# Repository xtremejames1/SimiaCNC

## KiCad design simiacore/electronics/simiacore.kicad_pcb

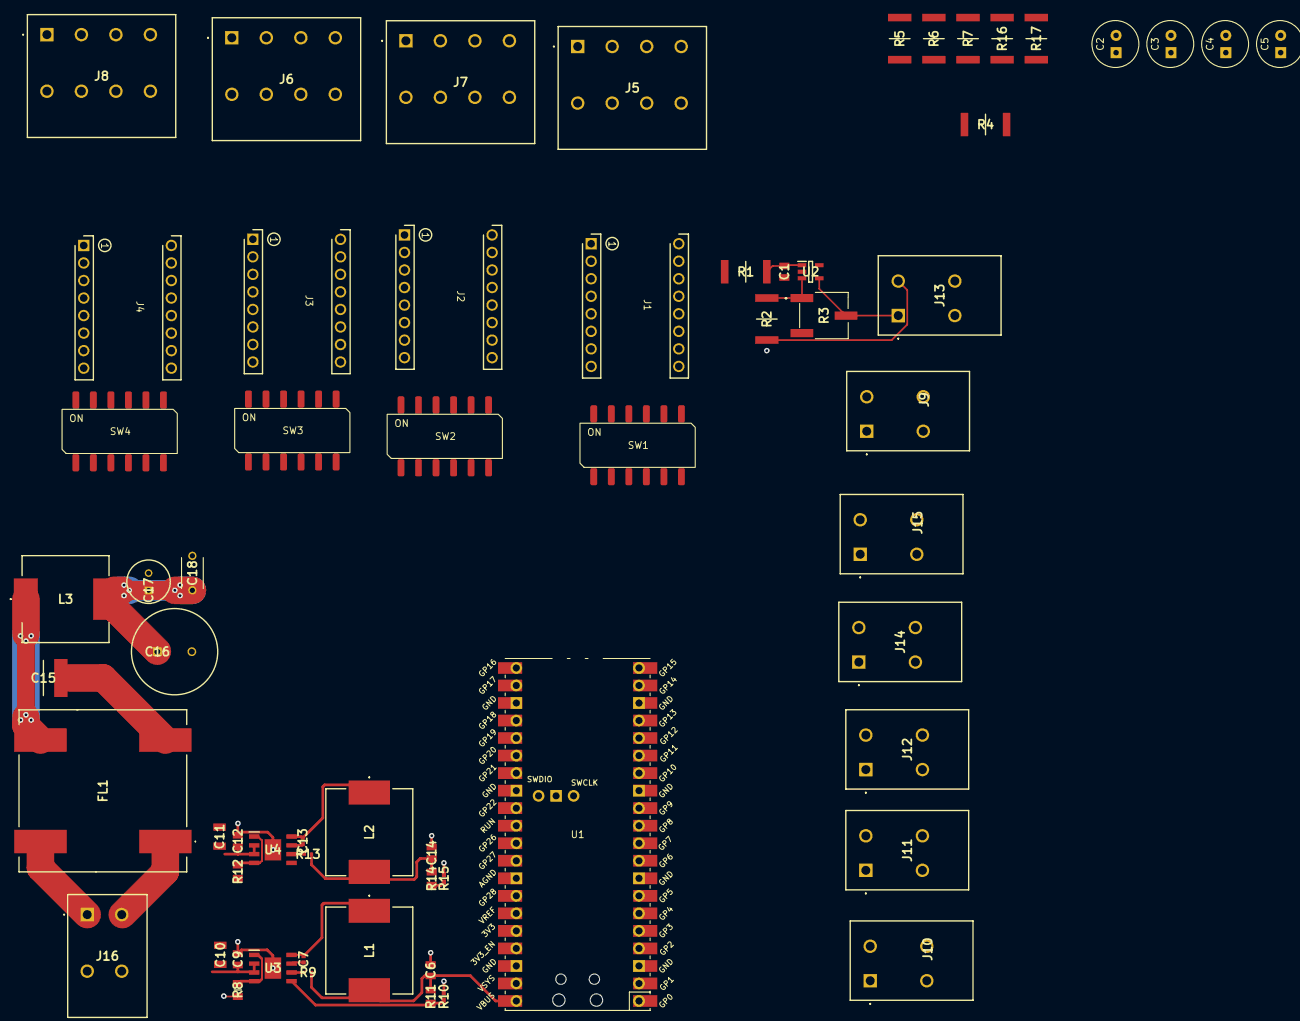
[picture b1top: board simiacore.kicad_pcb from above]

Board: 2 copper layers, 62 parts (0 on the bottom side), 75 nets.

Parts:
C1: 10uF; CAPC2012X145N
C2, C3, C4, C5: 100uF; MAL203859101E3
C6: 47uF; CAPC2012X145N
C7, C13: 100nF; CAPC1005X55N
C9, C12: 100nF; CAPC2012X145N
C10, C11: 3.3uF; CAPC3216X180N
C14: 22uF; CAPC2012X145N
C15: 22uF; CAPC6153X670N
C16: 330uF; CAPPRD500W65D1250H2700
C17: 10uF; CAPPRD250W50D630H1250
C18: 330nF; RDE5C1H103J1K1H03B
FL1: 240uH; PA5141305NLT
J1: X_STEP_DRIVER; 16pinStepperDriverHeader
J2: Y0_STEP_DRIVER; 16pinStepperDriverHeader
J3: Z_STEP_DRIVER; 16pinStepperDriverHeader
J4: Y1_STEP_DRIVER; 16pinStepperDriverHeader
J5: X_STEP; 1190299
J6: Y0_STEP; 1190299
J7: Z_STEP; 1190299
J8: Y1_STEP; 1190299
J9: X_LIM_PORT; 1190297
J10: Y0_LIM_PORT; 1190297
J11: Z_LIM_PORT; 1190297
J12: Y1_LIM_PORT; 1190297
J13: SPINDLE_SPEED; 1190297
J14: CYCLE_START_PORT; 1190297
J15: FEED_HOLD_PORT; 1190297
J16: 48VIN; 1190297
L1: 33uH; SRP1265WA4R7M
L2: 68uH; SRP1265WA4R7M
L3: 4.7uH; SRP1265WA4R7M
R1, R2: 1.5k; RESC6432X65N
R3: 5k_TRIM; 3361P1502GLF
R4, R5, R6, R7, R16, R17: 4.7k; RESC6432X65N
R8, R12: 64.9k; RESC2012X60N
R9, R13: 100k; ERJ2RKD1004X
R10, R15: 10k; RESC1005X35N
R11: 40.2k; RESC2012X60N
R14: 110k; RESC2012X60N
SW1, SW2, SW3, SW4: LOGIC_TOGGLE; CFS-0600TB
U1: PicoW; RPi_PicoW_SMD_TH
U2: NCS20231SN2T1G; SOT95P275X110-5N
U3, U4: LMR38010SDDAR; SOIC127P600X170-9N

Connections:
+3.3V: R4.1, R5.1, R6.1, R7.1, R16.1, R17.1, SW1.1, SW1.2, SW1.3, SW1.4, SW1.5, SW1.6, SW2.1, SW2.2, SW2.3, SW2.4, SW2.5, SW2.6, SW3.1, SW3.2, SW3.3, SW3.4, SW3.5, SW3.6, SW4.1, SW4.2, SW4.3, SW4.4, SW4.5, SW4.6, U1.36 (3V3)
+5V: C6.1, L1.2, R9.2, R11.1, U1.40 (VBUS)
+12V: C14.1, L2.2, R13.2, R14.1, U2.5 (VDD)
+48V: C2.1, C3.1, C4.1, C5.1, C9.1, C10.1, C11.1, C12.1, C16.1, C17.1, C18.1, J1.16, J2.16, J3.16, J4.16, L3.2, U3.2 (EN), U3.3 (VIN), U4.2 (EN), U4.3 (VIN)
/CYCLE_START: J14.1, R16.2, U1.22 (GPIO17)
/FEED_HOLD: J15.1, R17.2, U1.21 (GPIO16)
/Power Delivery/VIN: FL1.4, J16.1
/SPINDLE_PWM: R1.1, U1.20 (GPIO15)
/STEP_ENBL: J1.1, J2.1, J3.1, J4.1, U1.19 (GPIO14)
/Stepper Motor Drivers/X_A+: J1.11, J5.1
/Stepper Motor Drivers/X_A-: J1.12, J5.2
/Stepper Motor Drivers/X_B+: J1.14, J5.3
/Stepper Motor Drivers/X_B-: J1.13, J5.4
/Stepper Motor Drivers/Y0_A+: J2.11, J6.1
/Stepper Motor Drivers/Y0_A-: J2.12, J6.2
/Stepper Motor Drivers/Y0_B+: J2.14, J6.3
/Stepper Motor Drivers/Y0_B-: J2.13, J6.4
/Stepper Motor Drivers/Y1_A+: J4.11, J8.1
/Stepper Motor Drivers/Y1_A-: J4.12, J8.2
/Stepper Motor Drivers/Y1_B+: J4.14, J8.3
/Stepper Motor Drivers/Y1_B-: J4.13, J8.4
/Stepper Motor Drivers/Z_A+: J3.11, J7.1
/Stepper Motor Drivers/Z_A-: J3.12, J7.2
/Stepper Motor Drivers/Z_B+: J3.14, J7.3
/Stepper Motor Drivers/Z_B-: J3.13, J7.4
/X_DIR: J1.8, U1.9 (GPIO6)
/X_LIM: J9.1, R4.2, U1.24 (GPIO18)
/X_STEP: J1.7, U1.4 (GPIO2)
/Y0_DIR: J2.8, U1.10 (GPIO7)
/Y0_LIM: J10.1, R5.2, U1.25 (GPIO19)
/Y0_STEP: J2.7, J4.7, U1.5 (GPIO3)
/Y1_DIR: J4.8, U1.12 (GPIO9)
/Y1_LIM: J12.1, R7.2, U1.27 (GPIO21)
/Z_DIR: J3.8, U1.11 (GPIO8)
/Z_LIM: J11.1, R6.2, U1.26 (GPIO20)
/Z_STEP: J3.7, U1.6 (GPIO4)
GND: C1.2, C2.2, C3.2, C4.2, C5.2, C6.2, C9.2, C10.2, C11.2, C12.2, C14.2, C15.2, C16.2, C17.2, C18.2, FL1.1, FL1.2, J1.9, J1.15, J2.9, J2.15, J3.9, J3.15, J4.9, J4.15, J9.2, J10.2, J11.2, J12.2, J13.2, J14.2, J15.2, J16.2, R2.2, R8.2, R10.2, R12.2, R15.2, U2.2 (VSS), U3.9 (EP), U4.9 (EP)
unnamed: C15.1, FL1.3, L3.1
unnamed: J1.2, SW1.12
unnamed: J1.3, SW1.11
unnamed: J1.4, SW1.10
unnamed: J1.5, SW1.9
unnamed: J1.6, SW1.8
unnamed: J1.10, SW1.7
unnamed: J2.2, SW2.12
unnamed: J2.3, SW2.11
unnamed: J2.4, SW2.10
unnamed: J2.5, SW2.9
unnamed: J2.6, SW2.8
unnamed: J2.10, SW2.7
unnamed: J3.2, SW3.12
unnamed: J3.3, SW3.11
unnamed: J3.4, SW3.10
unnamed: J3.5, SW3.9
unnamed: J3.6, SW3.8
unnamed: J3.10, SW3.7
unnamed: J4.2, SW4.12
unnamed: J4.3, SW4.11
unnamed: J4.4, SW4.10
unnamed: J4.5, SW4.9
unnamed: J4.6, SW4.8
unnamed: J4.10, SW4.7
unnamed: J13.1, R3.2, U2.4 (IN-)
unnamed: R2.1, R3.1, U2.3 (IN+)
unnamed: C1.1, R1.2, U2.1 (OUT)
unnamed: C13.1, U3.7 (BOOT)
unnamed: R14.2, R15.1, U3.5 (FB)
unnamed: R12.1, U3.1 (GND), U3.4 (RT/SYNC)
unnamed: R13.1, U3.6 (PG)
unnamed: C13.2, L2.1, U3.8 (SW)
unnamed: C7.1, U4.7 (BOOT)
unnamed: R10.1, R11.2, U4.5 (FB)
unnamed: R8.1, U4.1 (GND), U4.4 (RT/SYNC)
unnamed: R9.1, U4.6 (PG)
unnamed: C7.2, L1.1, U4.8 (SW)

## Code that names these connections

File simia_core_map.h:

/*
  simiacore.h - driver code for SimiaCore CNC Controller Board

  Part of grblHAL

  Copyright (c) 2021-2023 Terje Io
  Copyright (c) 2021 Volksolive
  Copyright (c) 2023 James Xiao

  Grbl is free software: you can redistribute it and/or modify
  it under the terms of the GNU General Public License as published by
  the Free Software Foundation, either version 3 of the License, or
  (at your option) any later version.

  Grbl is distributed in the hope that it will be useful,
  but WITHOUT ANY WARRANTY; without even the implied warranty of
  MERCHANTABILITY or FITNESS FOR A PARTICULAR PURPOSE.  See the
  GNU General Public License for more details.

  You should have received a copy of the GNU General Public License
  along with Grbl.  If not, see <http://www.gnu.org/licenses/>.
*/

#if TRINAMIC_ENABLE
#error Trinamic plugin not supported!
#endif

#if N_ABC_MOTORS > 1
#error "Axis configuration is not supported!"
#endif

// Define step pulse output pins.
#define STEP_PORT               GPIO_PIO  // N_AXIS pin PIO SM
#define STEP_PINS_BASE          2         // N_AXIS number of consecutive pins are used by PIO

// Define step direction output pins.
#define DIRECTION_PORT          GPIO_OUTPUT
#define X_DIRECTION_PIN         6
#define Y_DIRECTION_PIN         7
#define Z_DIRECTION_PIN         8
#define DIRECTION_OUTMODE       GPIO_SHIFT5

// Define stepper driver enable/disable output pin.
#define ENABLE_PORT             GPIO_OUTPUT
#define STEPPERS_ENABLE_PIN     14

// Define shift register pins for limit switches.
#define QH_PIN                      20
#define CLK_PIN                     21
#define SH_LD_PIN                   22

#define QH_BIT (1<<QH_PIN)
#define CLK_BIT (1<<CLK_PIN)
#define SH_LD_BIT (1<<SH_LD_PIN)


// Define ganged axis or A axis step pulse and step direction output pins.
#define M3_AVAILABLE
#define M3_STEP_PIN             (STEP_PINS_BASE + 3)
#define M3_DIRECTION_PIN        (Z_DIRECTION_PIN + 1)

// Define spindle enable and spindle direction output pins.
#define SPINDLE_PORT            GPIO_OUTPUT
#define SPINDLE_ENABLE_PIN      26
#define SPINDLE_DIRECTION_PIN   27

// Define spindle PWM output pin.
#define SPINDLE_PWM_PORT        GPIO_OUTPUT
#define SPINDLE_PWM_PIN         15

// Define flood OR mist coolant enable output pins. ONLY ONE can be active at any time.
#define COOLANT_PORT            GPIO_OUTPUT
//#define COOLANT_FLOOD_PIN       16
#define COOLANT_MIST_PIN        16

// Define user-control controls (cycle start, reset, feed hold) input pins.
#define RESET_PIN               17
#define FEED_HOLD_PIN           18
#define CYCLE_START_PIN         19

//Define SD card pins
#if SDCARD_ENABLE
#define SPI_PORT            spi1
#define SD_SCK_PIN          10
#define SD_MOSI_PIN         11
#define SD_MISO_PIN         12
#define SD_CS_PIN           13

// Define probe switch input pin.
#define PROBE_PIN               22

#endif

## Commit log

2023-03-23 Edited config and my_machine.h
2023-03-25 Added code for simia_core.c for shift register limit switches, still need to implement fully, cleaned up simia_core_map.h
2023-03-25 ci: Add .deepsource.toml
2023-03-25 Added code for limit switches, realized we didnt need it, committing if we need it later.
2023-03-26 Added more stuff
2023-03-26 Organized
2023-03-27 Fixed limit switch code
2023-05-20 did some work
